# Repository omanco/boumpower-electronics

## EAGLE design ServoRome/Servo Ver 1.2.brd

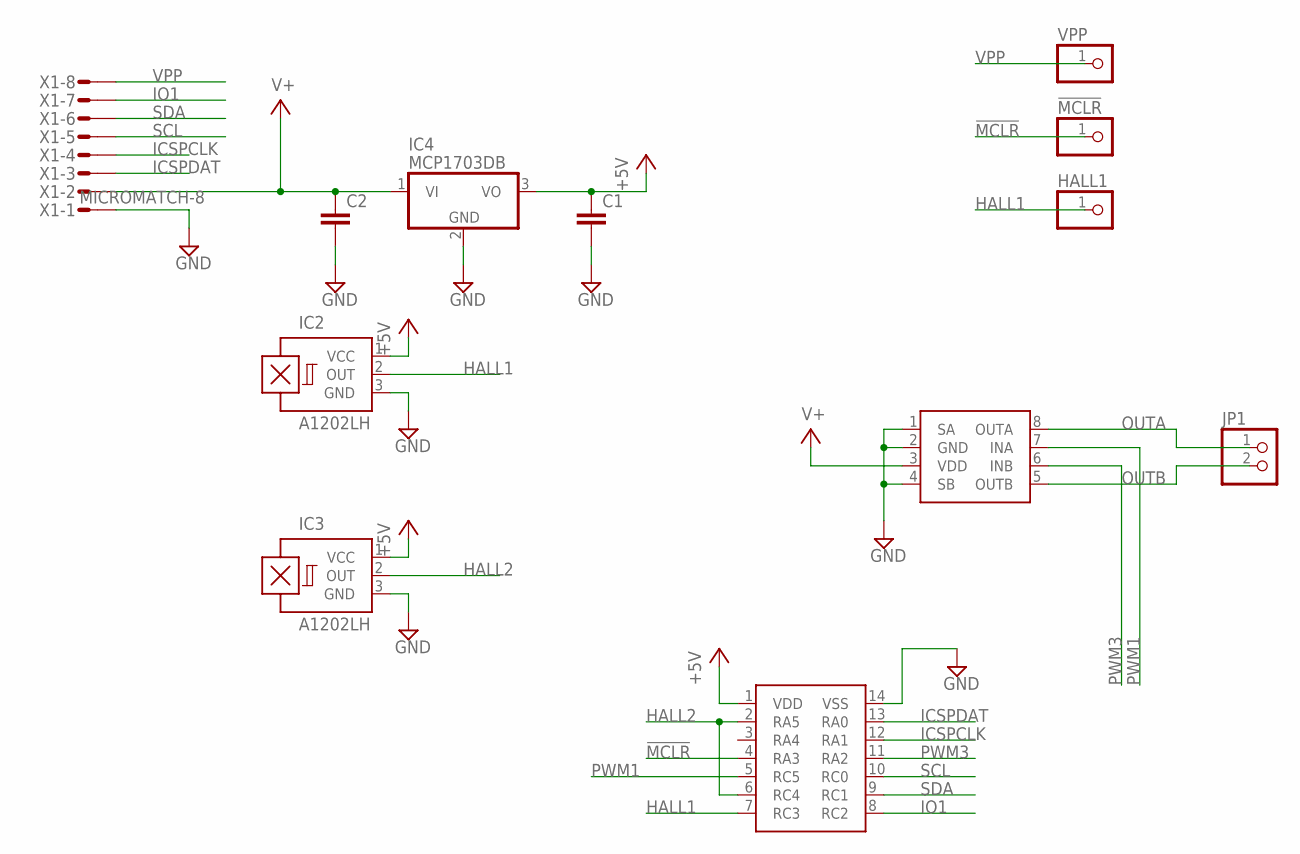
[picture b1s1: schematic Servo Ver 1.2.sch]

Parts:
!MCLR: PINHD-1X1; 1X01
C1, C2: C-EUC1206; C1206
HALL1: PINHD-1X1; 1X01
IC2, IC3: A1202LH; SOT23-W
IC4: MCP1703DB; SOT223
JP1: PINHD-1X2; 1X02
U$1: PIC16F1503SOIC; SO-14
U$2: SI9986SO8; SO-08
VPP: PINHD-1X1; 1X01
X1: MICROMATCH-8

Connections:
!MCLR: !MCLR.1, U$1.4 (RA3)
+5V: C1.1, IC2.1 (VCC), IC3.1 (VCC), IC4.3 (VO), U$1.1 (VDD)
GND: C1.2, C2.2, IC2.3 (GND), IC3.3 (GND), IC4.2 (GND), U$1.14 (VSS), U$2.1 (SA), U$2.2 (GND), U$2.4 (SB), X1.1
HALL1: HALL1.1, IC2.2 (OUT), U$1.7 (RC3)
HALL2: IC3.2 (OUT), U$1.2 (RA5), U$1.6 (RC4)
ICSPCLK: U$1.12 (RA1), X1.4
ICSPDAT: U$1.13 (RA0), X1.3
IO1: U$1.8 (RC2), X1.7
OUTA: JP1.1, U$2.8 (OUTA)
OUTB: JP1.2, U$2.5 (OUTB)
PWM1: U$1.5 (RC5), U$2.7 (INA)
PWM3: U$1.11 (RA2), U$2.6 (INB)
SCL: U$1.10 (RC0), X1.5
SDA: U$1.9 (RC1), X1.6
V+: C2.1, IC4.1 (VI), U$2.3 (VDD), X1.2
VPP: VPP.1, X1.8

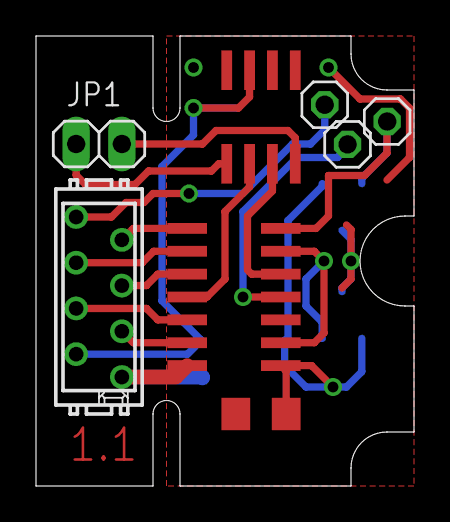
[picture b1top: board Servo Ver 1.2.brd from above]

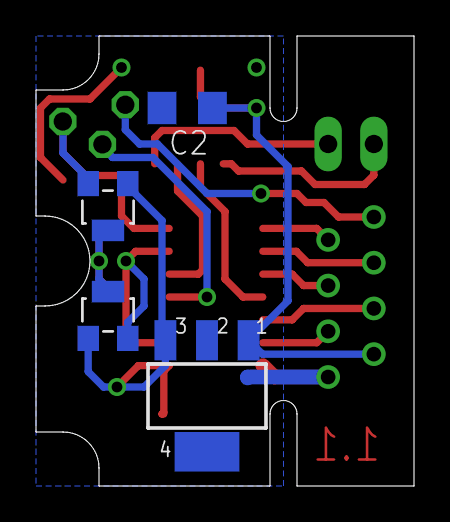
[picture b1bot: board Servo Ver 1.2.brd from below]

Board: 2 copper layers, 21.0 x 25.0 mm, 12 parts (4 on the bottom side), 16 nets.

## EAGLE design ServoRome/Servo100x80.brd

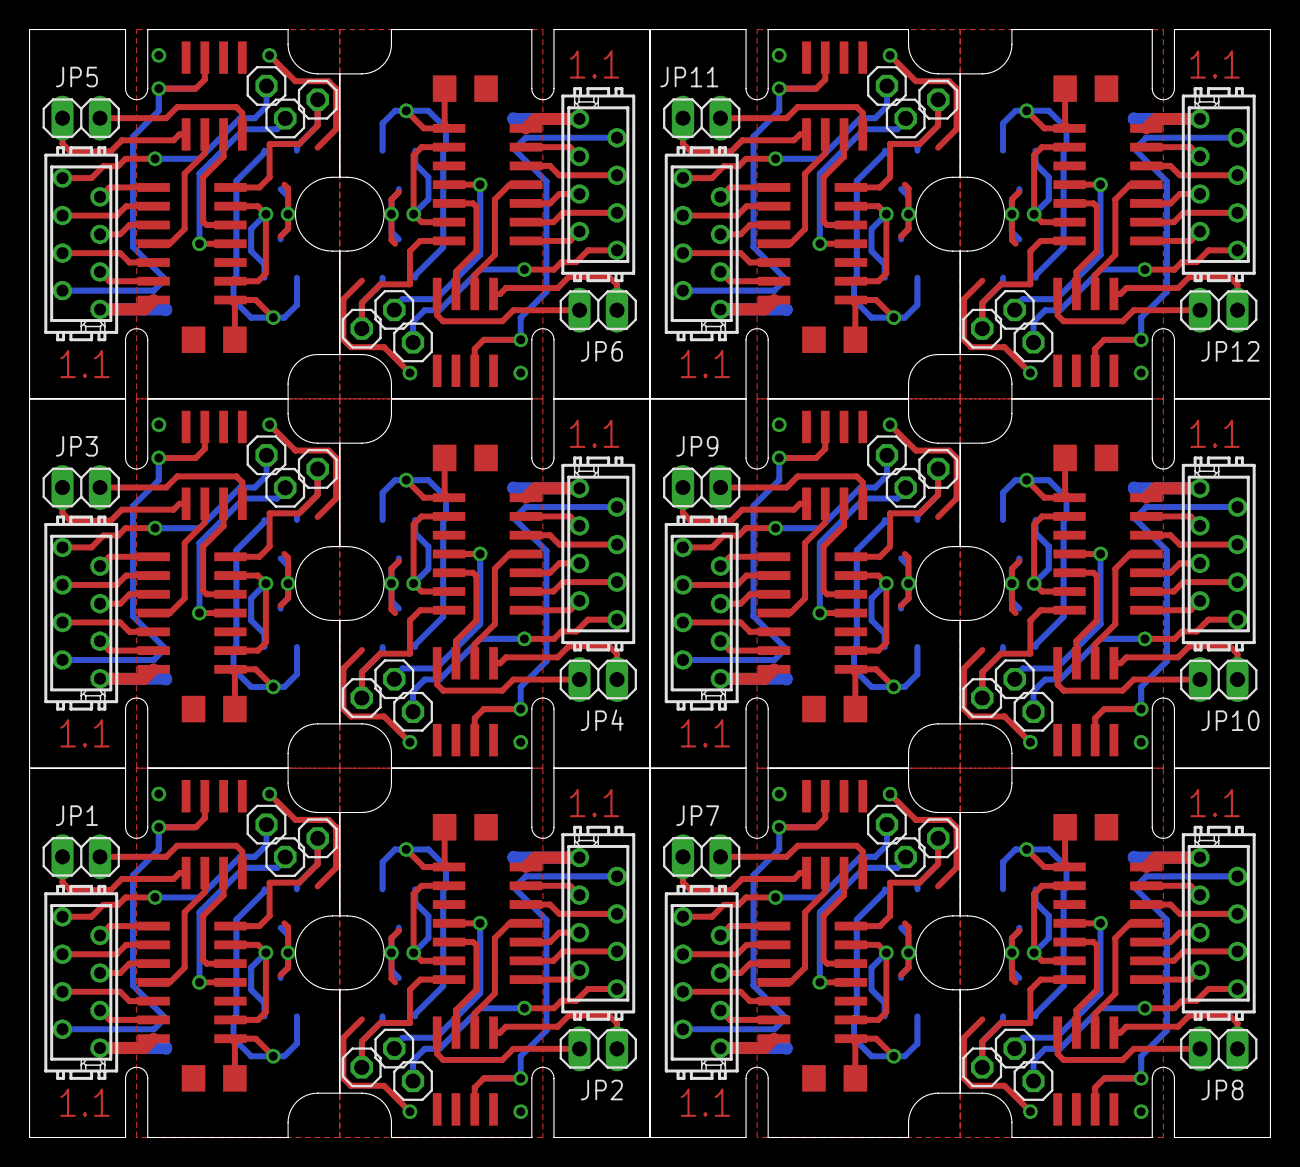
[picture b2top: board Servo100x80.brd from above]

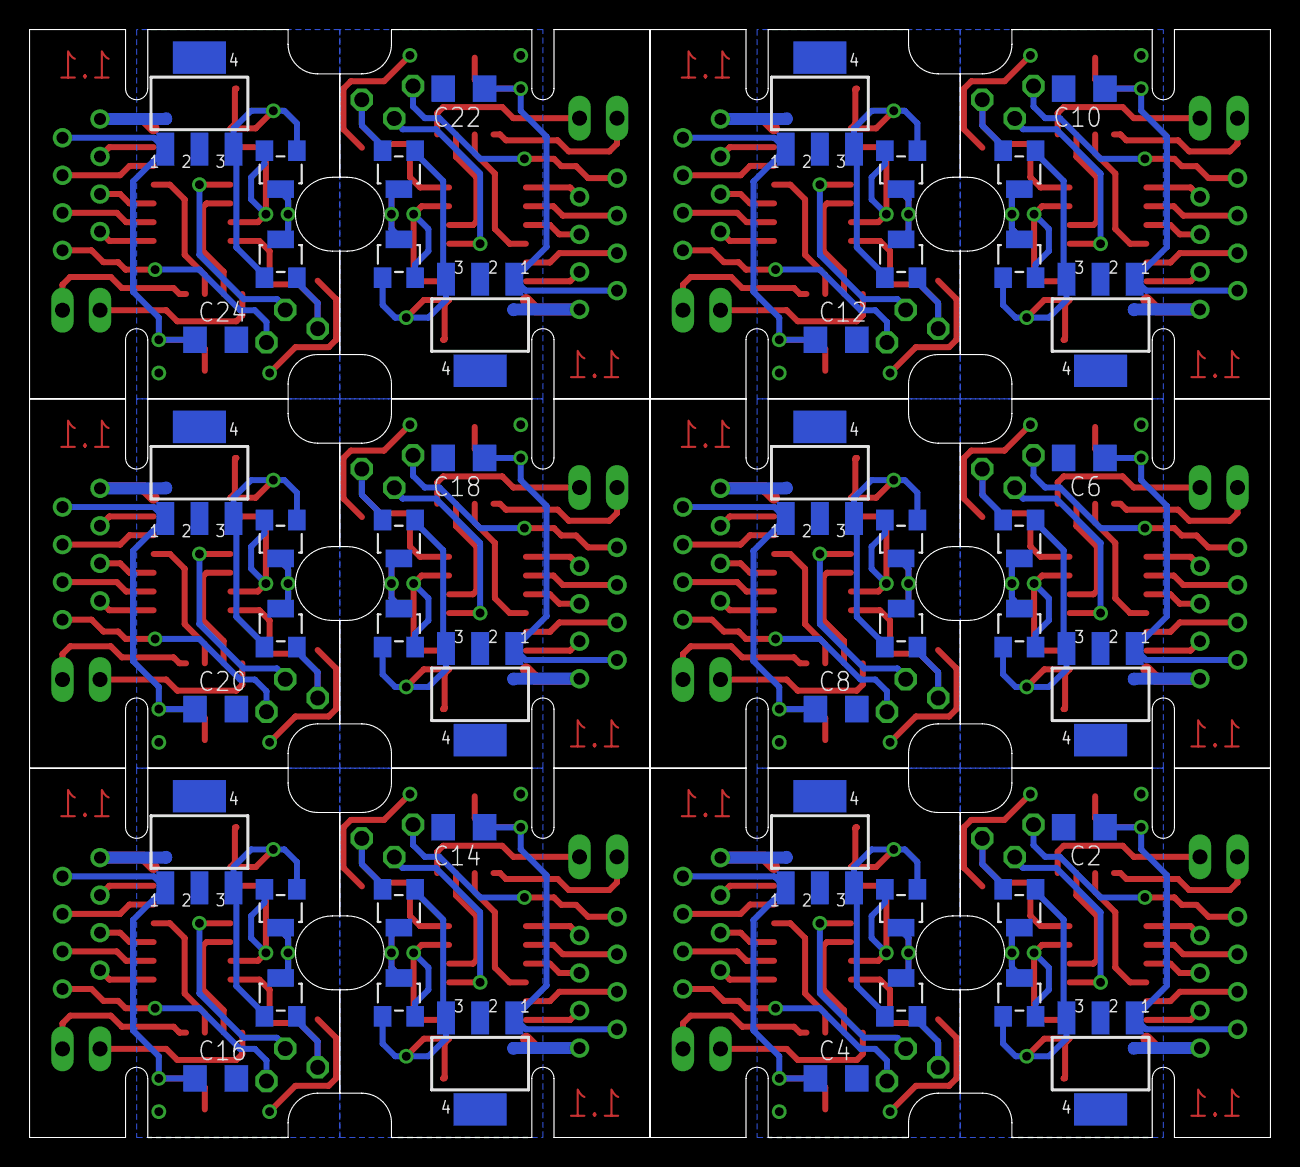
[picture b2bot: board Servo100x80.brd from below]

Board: 2 copper layers, 84.0 x 75.0 mm, 144 parts (48 on the bottom side), 192 nets.

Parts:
!MCLR, !MCLR1, !MCLR2, !MCLR3, !MCLR4, !MCLR5, !MCLR6, !MCLR7, !MCLR8, !MCLR9, !MCLR10, !MCLR11: 1X01
C1, C2, C3, C4, C5, C6, C7, C8, C9, C10, C11, C12, C13, C14, C15, C16, C17, C18, C19, C20, C21, C22, C23, C24: C1206
HALL1, HALL2, HALL3, HALL4, HALL5, HALL6, HALL7, HALL8, HALL9, HALL10, HALL11, HALL12: 1X01
IC1, IC2, IC3, IC5, IC7, IC8, IC10, IC11, IC13, IC14, IC16, IC17, IC19, IC20, IC22, IC23, IC25, IC26, IC28, IC29, IC31, IC32, IC34, IC35: A1202LH; SOT23-W
IC4, IC6, IC9, IC12, IC15, IC18, IC21, IC24, IC27, IC30, IC33, IC36: MCP1703DB; SOT223
JP1, JP2, JP3, JP4, JP5, JP6, JP7, JP8, JP9, JP10, JP11, JP12: 1X02
U$1, U$3, U$5, U$7, U$9, U$11, U$13, U$15, U$17, U$19, U$21, U$23: PIC16F1503SOIC; SO-14
U$2, U$4, U$6, U$8, U$10, U$12, U$14, U$16, U$18, U$20, U$22, U$24: SI9986SO8; SO-08
VPP, VPP1, VPP2, VPP3, VPP4, VPP5, VPP6, VPP7, VPP8, VPP9, VPP10, VPP11: 1X01
X1, X2, X3, X4, X5, X6, X7, X8, X9, X10, X11, X12: MICROMATCH-8

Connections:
!MCLR: !MCLR.1, U$1.4
!MCLR1: !MCLR1.1, U$3.4
!MCLR2: !MCLR2.1, U$5.4
!MCLR3: !MCLR3.1, U$7.4
!MCLR4: !MCLR4.1, U$9.4
!MCLR5: !MCLR5.1, U$11.4
!MCLR6: !MCLR6.1, U$13.4
!MCLR7: !MCLR7.1, U$15.4
!MCLR8: !MCLR8.1, U$17.4
!MCLR9: !MCLR9.1, U$19.4
!MCLR10: !MCLR10.1, U$21.4
!MCLR11: !MCLR11.1, U$23.4
+5V: C1.1, IC2.1, IC3.1, IC4.3, U$1.1
+5V1: C3.1, IC1.1, IC5.1, IC6.3, U$3.1
+5V2: C5.1, IC7.1, IC8.1, IC9.3, U$5.1
+5V3: C7.1, IC10.1, IC11.1, IC12.3, U$7.1
+5V4: C9.1, IC13.1, IC14.1, IC15.3, U$9.1
+5V5: C11.1, IC16.1, IC17.1, IC18.3, U$11.1
+5V6: C13.1, IC19.1, IC20.1, IC21.3, U$13.1
+5V7: C15.1, IC22.1, IC23.1, IC24.3, U$15.1
+5V8: C17.1, IC25.1, IC26.1, IC27.3, U$17.1
+5V9: C19.1, IC28.1, IC29.1, IC30.3, U$19.1
+5V10: C21.1, IC31.1, IC32.1, IC33.3, U$21.1
+5V11: C23.1, IC34.1, IC35.1, IC36.3, U$23.1
GND: C1.2, C2.2, IC2.3, IC3.3, IC4.2, U$1.14, U$2.1, U$2.2, U$2.4, X1.1
GND1: C3.2, C4.2, IC1.3, IC5.3, IC6.2, U$3.14, U$4.1, U$4.2, U$4.4, X2.1
GND2: C5.2, C6.2, IC7.3, IC8.3, IC9.2, U$5.14, U$6.1, U$6.2, U$6.4, X3.1
GND3: C7.2, C8.2, IC10.3, IC11.3, IC12.2, U$7.14, U$8.1, U$8.2, U$8.4, X4.1
GND4: C9.2, C10.2, IC13.3, IC14.3, IC15.2, U$9.14, U$10.1, U$10.2, U$10.4, X5.1
GND5: C11.2, C12.2, IC16.3, IC17.3, IC18.2, U$11.14, U$12.1, U$12.2, U$12.4, X6.1
GND6: C13.2, C14.2, IC19.3, IC20.3, IC21.2, U$13.14, U$14.1, U$14.2, U$14.4, X7.1
GND7: C15.2, C16.2, IC22.3, IC23.3, IC24.2, U$15.14, U$16.1, U$16.2, U$16.4, X8.1
GND8: C17.2, C18.2, IC25.3, IC26.3, IC27.2, U$17.14, U$18.1, U$18.2, U$18.4, X9.1
GND9: C19.2, C20.2, IC28.3, IC29.3, IC30.2, U$19.14, U$20.1, U$20.2, U$20.4, X10.1
GND10: C21.2, C22.2, IC31.3, IC32.3, IC33.2, U$21.14, U$22.1, U$22.2, U$22.4, X11.1
GND11: C23.2, C24.2, IC34.3, IC35.3, IC36.2, U$23.14, U$24.1, U$24.2, U$24.4, X12.1
HALL1: HALL1.1, IC2.2, U$1.7
HALL2: IC3.2, U$1.2, U$1.6
HALL3: IC5.2, U$3.2, U$3.6
HALL4: HALL2.1, IC1.2, U$3.7
HALL5: IC8.2, U$5.2, U$5.6
HALL6: HALL3.1, IC7.2, U$5.7
HALL7: IC11.2, U$7.2, U$7.6
HALL8: HALL4.1, IC10.2, U$7.7
HALL9: IC14.2, U$9.2, U$9.6
HALL10: HALL5.1, IC13.2, U$9.7
HALL11: IC17.2, U$11.2, U$11.6
HALL12: HALL6.1, IC16.2, U$11.7
HALL13: IC20.2, U$13.2, U$13.6
HALL14: HALL7.1, IC19.2, U$13.7
HALL15: IC23.2, U$15.2, U$15.6
HALL16: HALL8.1, IC22.2, U$15.7
HALL17: IC26.2, U$17.2, U$17.6
HALL18: HALL9.1, IC25.2, U$17.7
HALL19: IC29.2, U$19.2, U$19.6
HALL20: HALL10.1, IC28.2, U$19.7
HALL21: IC32.2, U$21.2, U$21.6
HALL22: HALL11.1, IC31.2, U$21.7
HALL23: IC35.2, U$23.2, U$23.6
HALL24: HALL12.1, IC34.2, U$23.7
ICSPCLK: U$1.12, X1.4
ICSPCLK1: U$3.12, X2.4
ICSPCLK2: U$5.12, X3.4
ICSPCLK3: U$7.12, X4.4
ICSPCLK4: U$9.12, X5.4
ICSPCLK5: U$11.12, X6.4
ICSPCLK6: U$13.12, X7.4
ICSPCLK7: U$15.12, X8.4
ICSPCLK8: U$17.12, X9.4
ICSPCLK9: U$19.12, X10.4
ICSPCLK10: U$21.12, X11.4
ICSPCLK11: U$23.12, X12.4
ICSPDAT: U$1.13, X1.3
ICSPDAT1: U$3.13, X2.3
ICSPDAT2: U$5.13, X3.3
ICSPDAT3: U$7.13, X4.3
ICSPDAT4: U$9.13, X5.3
ICSPDAT5: U$11.13, X6.3
ICSPDAT6: U$13.13, X7.3
ICSPDAT7: U$15.13, X8.3
ICSPDAT8: U$17.13, X9.3
ICSPDAT9: U$19.13, X10.3
ICSPDAT10: U$21.13, X11.3
ICSPDAT11: U$23.13, X12.3
IO1: U$1.8, X1.7
IO2: U$3.8, X2.7
IO3: U$5.8, X3.7
IO4: U$7.8, X4.7
IO5: U$9.8, X5.7
IO6: U$11.8, X6.7
IO7: U$13.8, X7.7
IO8: U$15.8, X8.7
IO9: U$17.8, X9.7
IO10: U$19.8, X10.7
IO11: U$21.8, X11.7
IO12: U$23.8, X12.7
OUTA: JP1.1, U$2.8
OUTA1: JP2.1, U$4.8
OUTA2: JP3.1, U$6.8
OUTA3: JP4.1, U$8.8
OUTA4: JP5.1, U$10.8
OUTA5: JP6.1, U$12.8
OUTA6: JP7.1, U$14.8
OUTA7: JP8.1, U$16.8
OUTA8: JP9.1, U$18.8
OUTA9: JP10.1, U$20.8
OUTA10: JP11.1, U$22.8
OUTA11: JP12.1, U$24.8
OUTB: JP1.2, U$2.5
OUTB1: JP2.2, U$4.5
OUTB2: JP3.2, U$6.5
OUTB3: JP4.2, U$8.5
OUTB4: JP5.2, U$10.5
OUTB5: JP6.2, U$12.5
OUTB6: JP7.2, U$14.5
OUTB7: JP8.2, U$16.5
OUTB8: JP9.2, U$18.5
OUTB9: JP10.2, U$20.5
OUTB10: JP11.2, U$22.5
OUTB11: JP12.2, U$24.5
PWM1: U$1.5, U$2.7
PWM2: U$3.11, U$4.6
PWM3: U$1.11, U$2.6
PWM4: U$3.5, U$4.7
PWM5: U$5.11, U$6.6
PWM6: U$5.5, U$6.7
PWM7: U$7.11, U$8.6
PWM8: U$7.5, U$8.7
PWM9: U$9.11, U$10.6
PWM10: U$9.5, U$10.7
PWM11: U$11.11, U$12.6
PWM12: U$11.5, U$12.7
PWM13: U$13.11, U$14.6
PWM14: U$13.5, U$14.7
PWM15: U$15.11, U$16.6
PWM16: U$15.5, U$16.7
PWM17: U$17.11, U$18.6
PWM18: U$17.5, U$18.7
PWM19: U$19.11, U$20.6
PWM20: U$19.5, U$20.7
PWM21: U$21.11, U$22.6
PWM22: U$21.5, U$22.7
PWM23: U$23.11, U$24.6
PWM24: U$23.5, U$24.7
SCL: U$1.10, X1.5
SCL1: U$3.10, X2.5
SCL2: U$5.10, X3.5
SCL3: U$7.10, X4.5
SCL4: U$9.10, X5.5
SCL5: U$11.10, X6.5
SCL6: U$13.10, X7.5
SCL7: U$15.10, X8.5
SCL8: U$17.10, X9.5
SCL9: U$19.10, X10.5
SCL10: U$21.10, X11.5
SCL11: U$23.10, X12.5
SDA: U$1.9, X1.6
SDA1: U$3.9, X2.6
SDA2: U$5.9, X3.6
SDA3: U$7.9, X4.6
SDA4: U$9.9, X5.6
SDA5: U$11.9, X6.6
SDA6: U$13.9, X7.6
SDA7: U$15.9, X8.6
SDA8: U$17.9, X9.6
SDA9: U$19.9, X10.6
SDA10: U$21.9, X11.6
SDA11: U$23.9, X12.6
V+: C2.1, IC4.1, U$2.3, X1.2
V+1: C4.1, IC6.1, U$4.3, X2.2
V+2: C6.1, IC9.1, U$6.3, X3.2
V+3: C8.1, IC12.1, U$8.3, X4.2
V+4: C10.1, IC15.1, U$10.3, X5.2
V+5: C12.1, IC18.1, U$12.3, X6.2
V+6: C14.1, IC21.1, U$14.3, X7.2
V+7: C16.1, IC24.1, U$16.3, X8.2
V+8: C18.1, IC27.1, U$18.3, X9.2
V+9: C20.1, IC30.1, U$20.3, X10.2
V+10: C22.1, IC33.1, U$22.3, X11.2
V+11: C24.1, IC36.1, U$24.3, X12.2
VPP: VPP.1, X1.8
VPP1: VPP1.1, X2.8
VPP2: VPP2.1, X3.8
VPP3: VPP3.1, X4.8
VPP4: VPP4.1, X5.8
VPP5: VPP5.1, X6.8
VPP6: VPP6.1, X7.8
VPP7: VPP7.1, X8.8
VPP8: VPP8.1, X9.8
VPP9: VPP9.1, X10.8
VPP10: VPP10.1, X11.8
VPP11: VPP11.1, X12.8

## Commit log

2011-02-21 Initial directory structure.
2011-02-21 Boe-Bot
2011-02-21 Div projects
2011-02-23 PinguiBot
2011-03-17 Second RS485 connector
2011-06-25 Gerber files added
2015-06-04 Migrating wiki contents from Google Code
